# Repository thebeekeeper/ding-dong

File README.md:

## r0 Assembly Notes

- I forgot IO8 needs to be high at boot to be able to program the part.  Currently connected to c6, so I won't be able to use that output for now.
- I don't have the right inductors for the regulator on hand, so I used 33uH for both.  3.3v works, but 12v is down around 1v.  I'll try the correct inductor, but it might be easier to use a 12v wall wart.  Doorbell transformers give AC, so I'd have to convert it anyways.

## Changes for r1

- Removed the 12V regulator and added a barrel jack for power input.  
- Moved the `c6` signal from IO8 to IO18.  `IO8` needs to be high to program the esp32.  I'm not planning on using USB, so IO18 should be fine.
- Added a screw terminal to signal that the button has been pressed and wired it to IO19.  Added a pull-up on the signal, but I'm not sure if I'll need it.

I wasn't thinking about how the signal will come from the button, but in a typical doorbell, the button closes a circuit that will supply us with 12-14V AC.  I could put a bridge rectifier circuit in, and just use that but then I will only have power while the button is held down.  I think the best option would to use  12v wall wart and signal the bell to activate either by:
	1. A small circuit that detects when the low side of the doorbell transformer turns on and sends a 3.3v signal to my board
	2. Something wireless
So either way, the driver board will just expect a 3.3v signal and start the sequence when it gets the signal

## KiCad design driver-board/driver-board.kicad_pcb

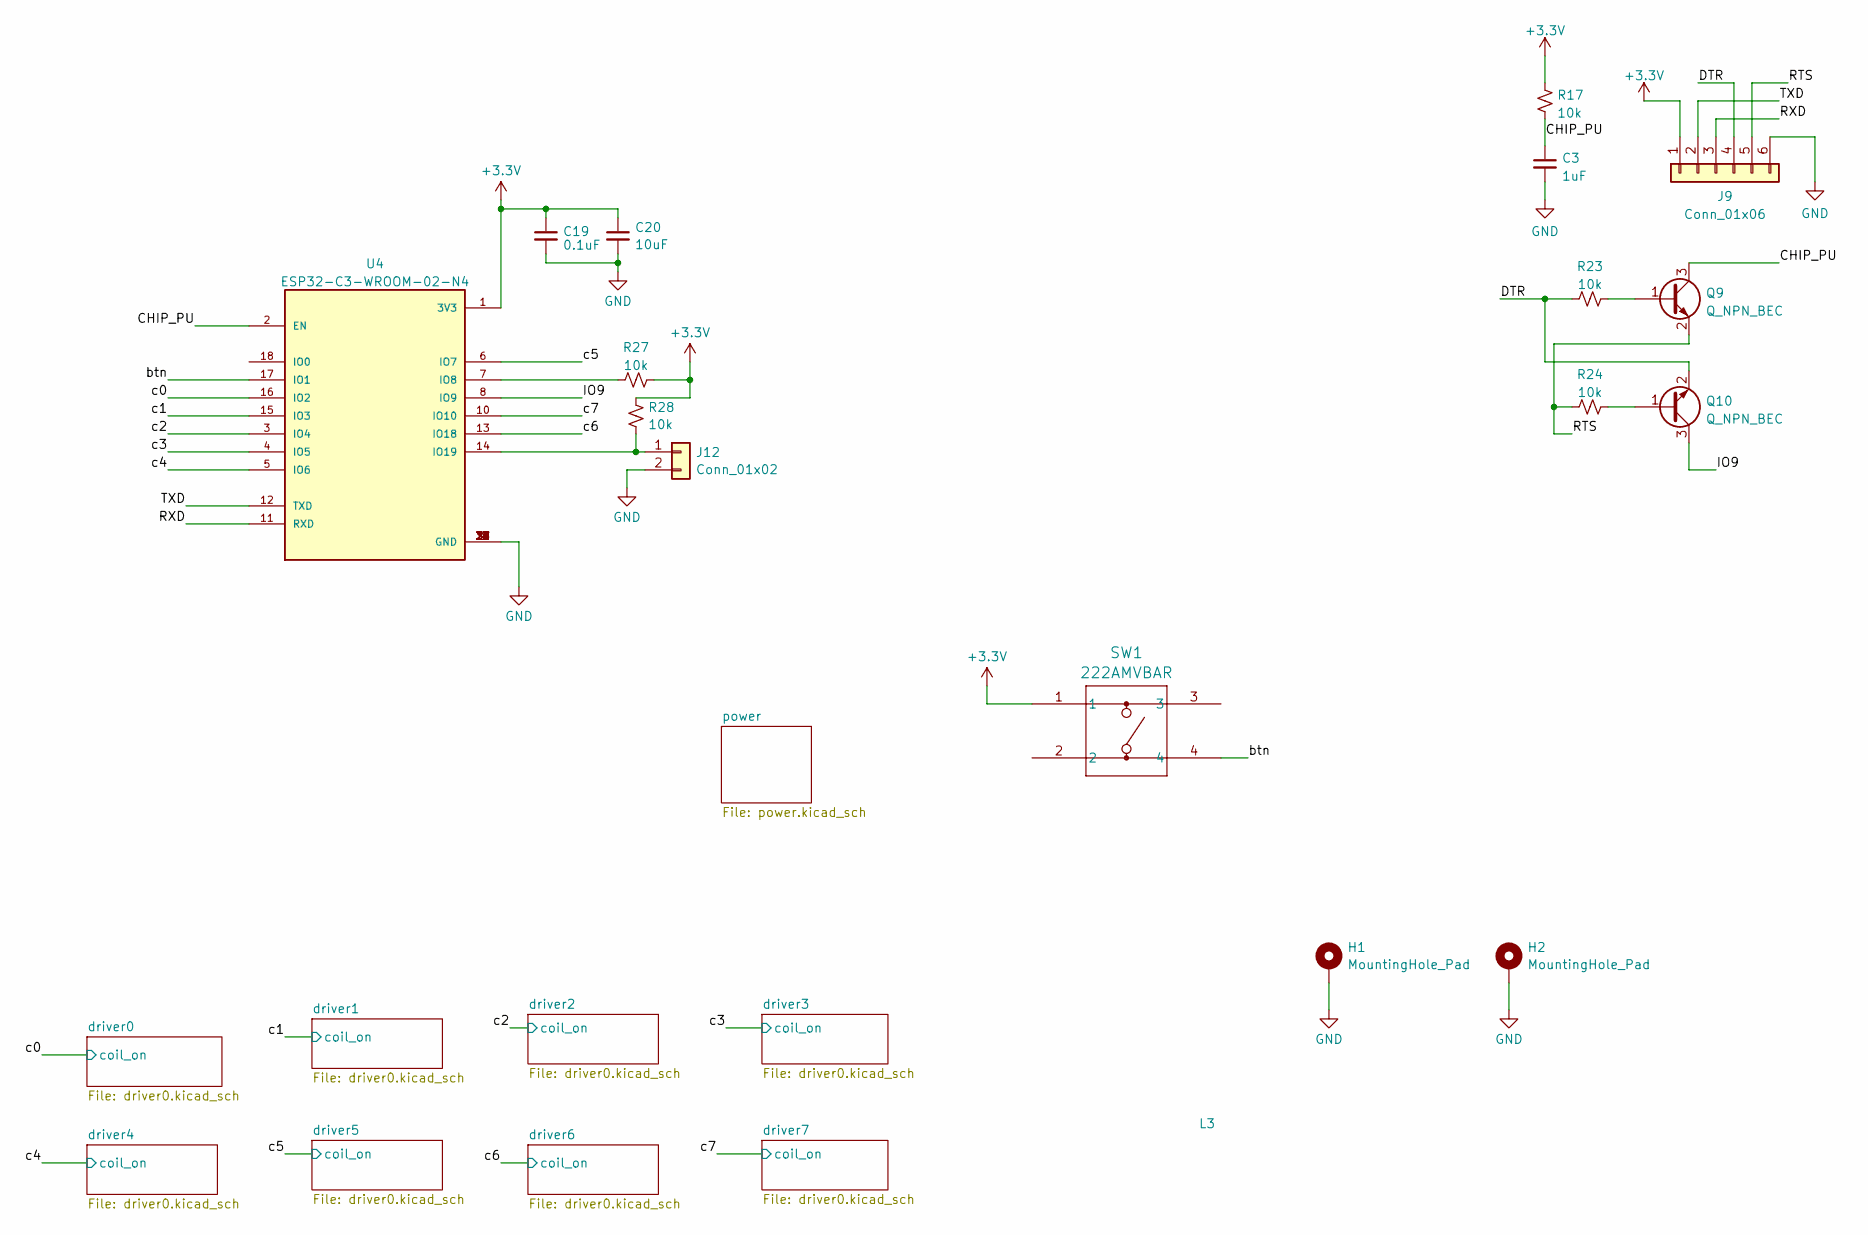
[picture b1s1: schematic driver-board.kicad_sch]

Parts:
C3: 1uF; C_0805_2012Metric; ManufacturerPartNumber CL21B105KOFNFNE
C19: 0.1uF; C_0603_1608Metric
C20: 10uF; C_0603_1608Metric
H1, H2: MountingHole_Pad; MountingHole_3.2mm_M3_Pad
J9: Conn_01x06; PinHeader_1x06_P2.54mm_Vertical; ManufacturerPartNumber TSW-106-07-G-S
J12: Conn_01x02; PhoenixContact_MCV_1,5_2-GF-3.81_1x02_P3.81mm_Vertical_Thre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
L3: bird
Q9, Q10: Q_NPN_BEC; SOT-23; ManufacturerPartNumber MMSS8050-H-TP
R17, R23, R24, R27, R28: 10k; R_0805_2012Metric; ManufacturerPartNumber RMCF0805FT10K0
SW1: 222AMVBAR; SO4_222A-M-V-B_CTS; ManufacturerPartNumber 222AMVBAR
U4: ESP32-C3-WROOM-02-N4; MODULE_ESP32-C3-WROOM-02-H4; ManufacturerPartNumber ESP32-C3-WROOM-02-N4

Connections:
+3.3V: C19.1, C20.1, J9.1, R17.1, R27.2, R28.2, SW1.1, U4.1 (3V3); also elsewhere on the board
/CHIP_PU: C3.1, Q9.3 (C), R17.2, U4.2 (EN)
/DTR: J9.4, Q10.2 (E), R23.1
/IO9: Q10.3 (C), U4.8 (IO9)
/RTS: J9.5, Q9.2 (E), R24.1
/RXD: J9.3, U4.11 (RXD)
/TXD: J9.2, U4.12 (TXD)
/btn: SW1.4, U4.17 (IO1)
/c0: U4.16 (IO2); also elsewhere on the board
/c1: U4.15 (IO3); also elsewhere on the board
/c2: U4.3 (IO4); also elsewhere on the board
/c3: U4.4 (IO5); also elsewhere on the board
/c4: U4.5 (IO6); also elsewhere on the board
/c5: U4.6 (IO7); also elsewhere on the board
/c6: U4.13 (IO18); also elsewhere on the board
/c7: U4.10 (IO10); also elsewhere on the board
GND: C3.2, C19.2, C20.2, H1.1, H2.1, J9.6, J12.2, U4.9 (GND), U4.19 (GND), U4.20 (GND), U4.21 (GND), U4.22 (GND), U4.23 (GND), U4.24 (GND), U4.25 (GND), U4.26 (GND), U4.27 (GND), U4.28 (GND), U4.29 (GND), U4.30 (GND), U4.31 (GND), U4.32 (GND), U4.33 (GND), U4.34 (GND), U4.35 (GND), U4.36 (GND), U4.37 (GND), U4.38 (GND), U4.39 (GND); also elsewhere on the board
unnamed: J12.1, R28.1, U4.14 (IO19)
unnamed: Q9.1 (B), R23.2
unnamed: Q10.1 (B), R24.2
unnamed: R27.1, U4.7 (IO8)

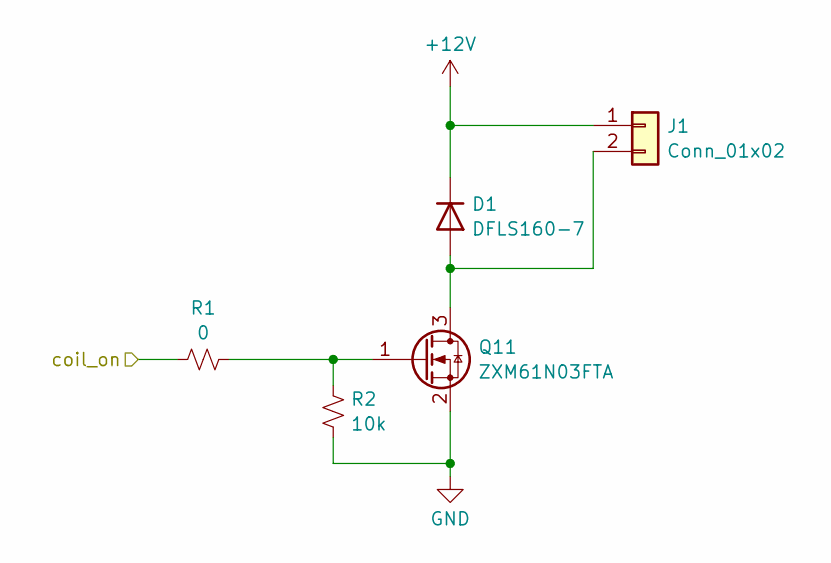
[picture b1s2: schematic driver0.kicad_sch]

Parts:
D1: DFLS160-7; D_PowerDI-123
J1: Conn_01x02; JST_PH_B2B-PH-K_1x02_P2.00mm_Vertical
Q11: ZXM61N03FTA; SOT-23-3
R1: 0; R_0805_2012Metric
R2: 10k; R_0805_2012Metric

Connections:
+12V: D1.1 (K), J1.1; also elsewhere on the board
/c0: R1.1; also elsewhere on the board
GND: Q11.2 (S), R2.1; also elsewhere on the board
unnamed: D1.2 (A), J1.2, Q11.3 (D)
unnamed: Q11.1 (G), R1.2, R2.2

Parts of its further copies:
D2, D3, D4, D5, D6, D7, D8: DFLS160-7; D_PowerDI-123
J2, J3, J4, J5, J6, J7, J8: Conn_01x02; JST_PH_B2B-PH-K_1x02_P2.00mm_Vertical
Q12, Q13, Q14, Q15, Q16, Q17, Q18: ZXM61N03FTA; SOT-23-3
R4, R6, R8, R10, R12, R14, R16: 10k; R_0805_2012Metric

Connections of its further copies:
+12V: D2.1 (K), D3.1 (K), D4.1 (K), D5.1 (K), D6.1 (K), D7.1 (K), D8.1 (K), J2.1, J3.1, J4.1, J5.1, J6.1, J7.1, J8.1; also elsewhere on the board
GND: Q12.2 (S), Q13.2 (S), Q14.2 (S), Q15.2 (S), Q16.2 (S), Q17.2 (S), Q18.2 (S), R4.1, R6.1, R8.1, R10.1, R12.1, R14.1, R16.1; also elsewhere on the board
unnamed: D2.2 (A), J2.2, Q12.3 (D)
unnamed: D3.2 (A), J3.2, Q13.3 (D)
unnamed: D4.2 (A), J4.2, Q14.3 (D)
unnamed: D5.2 (A), J5.2, Q15.3 (D)
unnamed: D6.2 (A), J6.2, Q16.3 (D)
unnamed: D7.2 (A), J7.2, Q17.3 (D)
unnamed: D8.2 (A), J8.2, Q18.3 (D)
unnamed 31: Q12.1 (G), R4.2; also elsewhere on the board
unnamed 32: Q13.1 (G), R6.2; also elsewhere on the board
unnamed 33: Q14.1 (G), R8.2; also elsewhere on the board
unnamed 34: Q15.1 (G), R10.2; also elsewhere on the board
unnamed 35: Q16.1 (G), R12.2; also elsewhere on the board
unnamed 36: Q17.1 (G), R14.2; also elsewhere on the board
unnamed 37: Q18.1 (G), R16.2; also elsewhere on the board

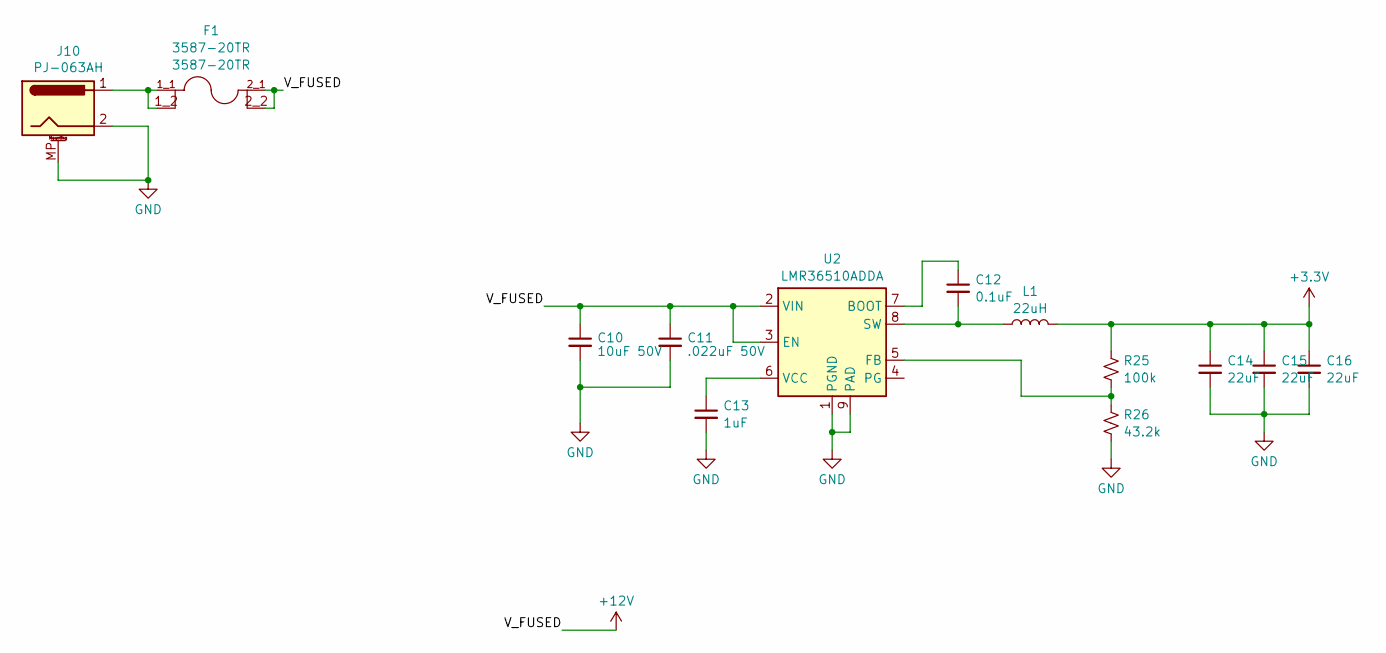
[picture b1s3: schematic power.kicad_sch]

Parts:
C10: 10uF 50V; C_1206_3216Metric; ManufacturerPartNumber CL31A106MBHNNNE
C11: .022uF 50V; C_1206_3216Metric; ManufacturerPartNumber 12065C223KAT4A
C12: 0.1uF; C_0805_2012Metric
C13: 1uF; C_0805_2012Metric
C14, C15, C16: 22uF; C_0805_2012Metric
F1: 3587-20TR; FUSE_3587; ManufacturerPartNumber 3587-20TR
J10: PJ-063AH; BarrelJack_CUI_PJ-063AH_Horizontal; ManufacturerPartNumber PJ-063AH
L1: 22uH; SRN3010C2R2M
R25: 100k; R_0805_2012Metric; ManufacturerPartNumber RMCF0805FT10K0
R26: 43.2k; R_0805_2012Metric; ManufacturerPartNumber RMCF0805FT10K0
U2: LMR36510ADDA; Texas_HTSOP-8-1EP_3.9x4.9mm_P1.27mm_EP2.95x4.9mm_Mask2.4x3.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

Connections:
+3.3V: C14.1, C15.1, C16.1, L1.2, R25.2; also elsewhere on the board
+12V: C10.1, C11.1, F1.2_1, F1.2_2, U2.2 (VIN), U2.3 (EN); also elsewhere on the board
GND: C10.2, C11.2, C13.2, C14.2, C15.2, C16.2, J10.2, J10.MP (MountPin), R26.1, U2.1 (PGND), U2.9 (PAD); also elsewhere on the board
unnamed: F1.1_1, F1.1_2, J10.1
unnamed: C12.1, U2.7 (BOOT)
unnamed: R25.1, R26.2, U2.5 (FB)
unnamed: C12.2, L1.1, U2.8 (SW)
unnamed: C13.1, U2.6 (VCC)

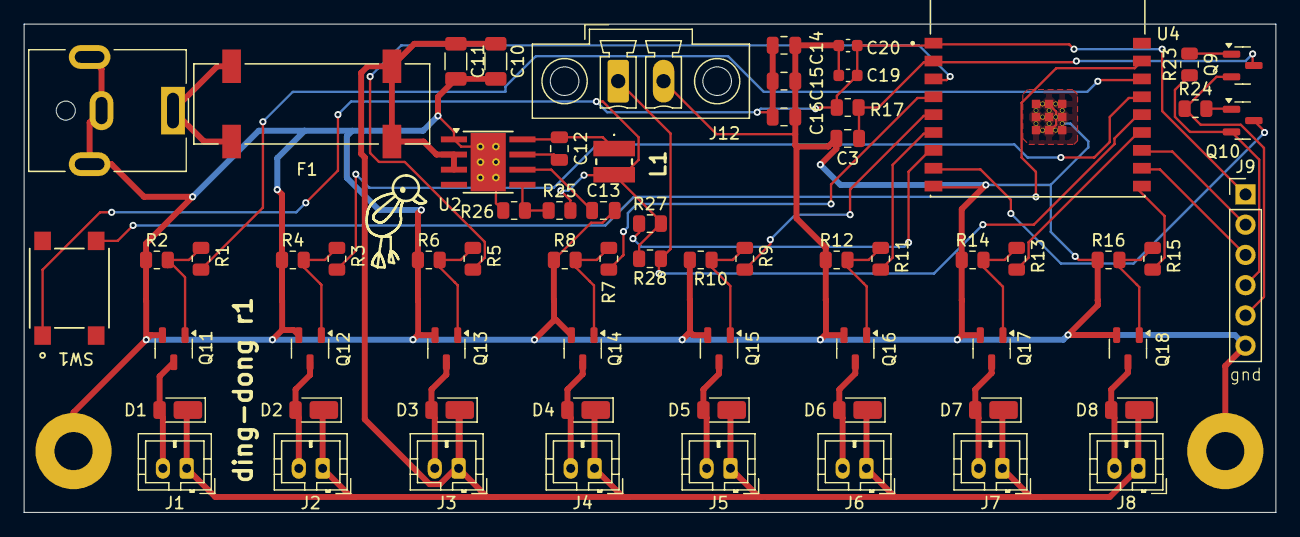
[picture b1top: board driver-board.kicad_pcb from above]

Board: 2 copper layers, 105.1 x 41.0 mm, 70 parts (0 on the bottom side), 43 nets.

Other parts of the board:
R3, R5, R7, R9, R11, R13, R15: 4.7k; R_0805_2012Metric

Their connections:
/c1: R3.1; also elsewhere on the board
/c2: R5.1; also elsewhere on the board
/c3: R7.1; also elsewhere on the board
/c4: R9.1; also elsewhere on the board
/c5: R11.1; also elsewhere on the board
/c6: R13.1; also elsewhere on the board
/c7: R15.1; also elsewhere on the board
unnamed 31: R3.2; also elsewhere on the board
unnamed 32: R5.2; also elsewhere on the board
unnamed 33: R7.2; also elsewhere on the board
unnamed 34: R9.2; also elsewhere on the board
unnamed 35: R11.2; also elsewhere on the board
unnamed 36: R13.2; also elsewhere on the board
unnamed 37: R15.2; also elsewhere on the board

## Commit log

2025-06-16 initial add
2025-06-16 schematic updates for r1
2025-06-16 updated layout
2025-07-04 new board
